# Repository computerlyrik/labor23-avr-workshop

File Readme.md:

TODO
====
- Strombuchse hinzufügen
- Quartz aussuchen und einfügen
- Board malen

libs
-----
ftp://ftp.cadsoft.de/eagle/userfiles/libraries/avr-7.lbr

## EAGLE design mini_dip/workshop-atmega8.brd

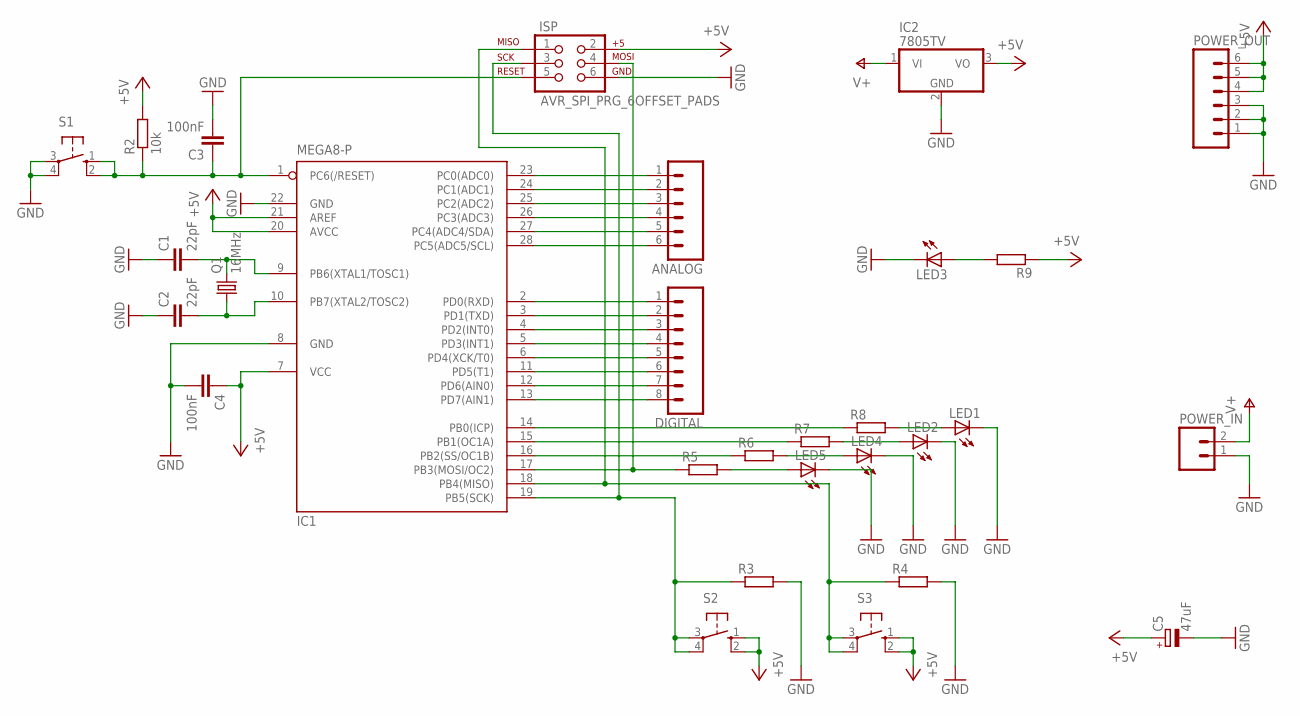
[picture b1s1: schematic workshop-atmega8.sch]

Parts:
ANALOG: M06LOCK_LONGPADS; 1X06_LOCK_LONGPADS
C1, C2: 22pF; C025-025X050
C3, C4: 100nF; C025-025X050
C5: 47uF; E2,5-7
DIGITAL: M08LOCK_LONGPADS; 1X08_LOCK_LONGPADS
IC1: MEGA8-P; DIL28-3
IC2: 7805TV; TO220V
ISP: AVR_SPI_PRG_6OFFSET_PADS; 2X3_OFFSET
LED1, LED2, LED3, LED4, LED5: LED5MM
POWER_IN: M02LOCK_LONGPADS; 1X02_LOCK_LONGPADS
POWER_OUT: M06LOCK_LONGPADS; 1X06_LOCK_LONGPADS
Q1: 16MHz; HC49/S
R2: 10k; 0207/10
R3, R4, R5, R6, R7, R8, R9: R-EU_0207/10; 0207/10
S1, S2, S3: 10-XX; B3F-10XX

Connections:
+5V: C4.1, C5.+, IC1.7 (VCC), IC1.20 (AVCC), IC1.21 (AREF), IC2.3 (VO), ISP.2, POWER_OUT.4, POWER_OUT.5, POWER_OUT.6, R2.2, R9.1, S2.1 (S), S2.2 (S1), S3.1 (S), S3.2 (S1)
GND: C1.1, C2.1, C3.2, C4.2, C5.-, IC1.8 (GND), IC1.22 (GND), IC2.2 (GND), ISP.6, LED1.K (C), LED2.K (C), LED3.K (C), LED4.K (C), LED5.K (C), POWER_IN.1, POWER_OUT.1, POWER_OUT.2, POWER_OUT.3, R3.2, R4.2, S1.3, S1.4 (P1)
unnamed: C1.2, IC1.9 (PB6(XTAL1/TOSC1)), Q1.2
unnamed: C2.2, IC1.10 (PB7(XTAL2/TOSC2)), Q1.1
unnamed: C3.1, IC1.1 (PC6(/RESET)), ISP.5, R2.1, S1.1 (S), S1.2 (S1)
unnamed: IC1.17 (PB3(MOSI/OC2)), ISP.4, R5.1
unnamed: LED3.A, R9.2
unnamed: LED1.A, R8.2
unnamed: ANALOG.1, IC1.23 (PC0(ADC0))
unnamed: ANALOG.2, IC1.24 (PC1(ADC1))
unnamed: ANALOG.3, IC1.25 (PC2(ADC2))
unnamed: ANALOG.4, IC1.26 (PC3(ADC3))
unnamed: ANALOG.5, IC1.27 (PC4(ADC4/SDA))
unnamed: ANALOG.6, IC1.28 (PC5(ADC5/SCL))
unnamed: LED2.A, R7.2
unnamed: IC1.18 (PB4(MISO)), ISP.1, R4.1, S3.3, S3.4 (P1)
unnamed: IC1.15 (PB1(OC1A)), R7.1
unnamed: IC1.14 (PB0(ICP)), R8.1
unnamed: LED4.A, R6.2
unnamed: DIGITAL.1, IC1.2 (PD0(RXD))
unnamed: LED5.A, R5.2
unnamed: DIGITAL.2, IC1.3 (PD1(TXD))
unnamed: IC1.19 (PB5(SCK)), ISP.3, R3.1, S2.3, S2.4 (P1)
unnamed: DIGITAL.3, IC1.4 (PD2(INT0))
unnamed: DIGITAL.4, IC1.5 (PD3(INT1))
unnamed: DIGITAL.5, IC1.6 (PD4(XCK/T0))
unnamed: DIGITAL.6, IC1.11 (PD5(T1))
unnamed: DIGITAL.7, IC1.12 (PD6(AIN0))
unnamed: DIGITAL.8, IC1.13 (PD7(AIN1))
unnamed: IC1.16 (PB2(SS/OC1B)), R6.1
V+: IC2.1 (VI), POWER_IN.2

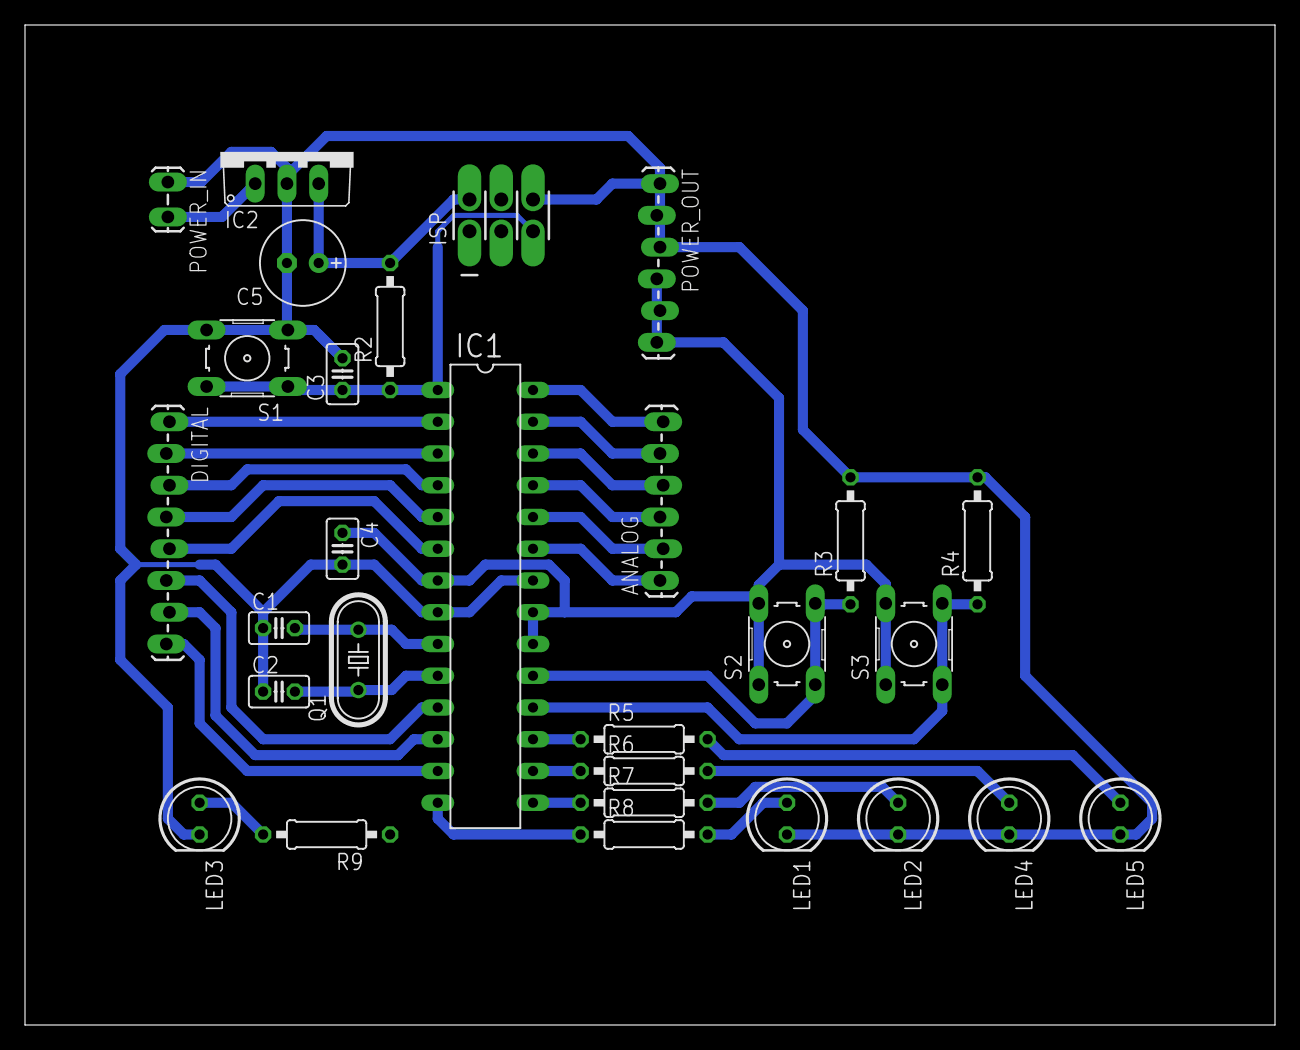
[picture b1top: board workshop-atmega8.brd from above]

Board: 2 copper layers, 100.0 x 80.0 mm, 29 parts (0 on the bottom side), 31 nets.

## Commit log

2013-02-14 added some readme
2013-02-14 added basic board scheme
2013-02-14 smaller fixes
2013-02-14 updated readme, small fixes on schema
2013-03-08 added eagle files from tom

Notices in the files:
parts and their libraries:
SparkFun: Licensing: CC v3.0 Share-Alike You are welcome to use this library for commercial purposes.
